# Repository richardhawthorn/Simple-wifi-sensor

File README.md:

### Description

Designed to collect and report various sensor readings over wifi.

### Sensors

- Temperature
- Humidity
- Light
- Vibration
- IR Receiver

### Other Features

- ESP8266
- 3.3V operation
- Mini USB power connector
- FTDI programming port
- IR Transmitter

### License

This work is licensed under a Creative Commons Attribution-ShareAlike 4.0 International License.

<br />
Designed by <a xmlns:cc="http://creativecommons.org/ns#" href="http://www.richardhawthorn.com" property="cc:attributionName" rel="cc:attributionURL" target="_blank">Richard Hawthorn</a><br />
<a rel="license" href="http://creativecommons.org/licenses/by-sa/4.0/" target="_blank">View License</a>

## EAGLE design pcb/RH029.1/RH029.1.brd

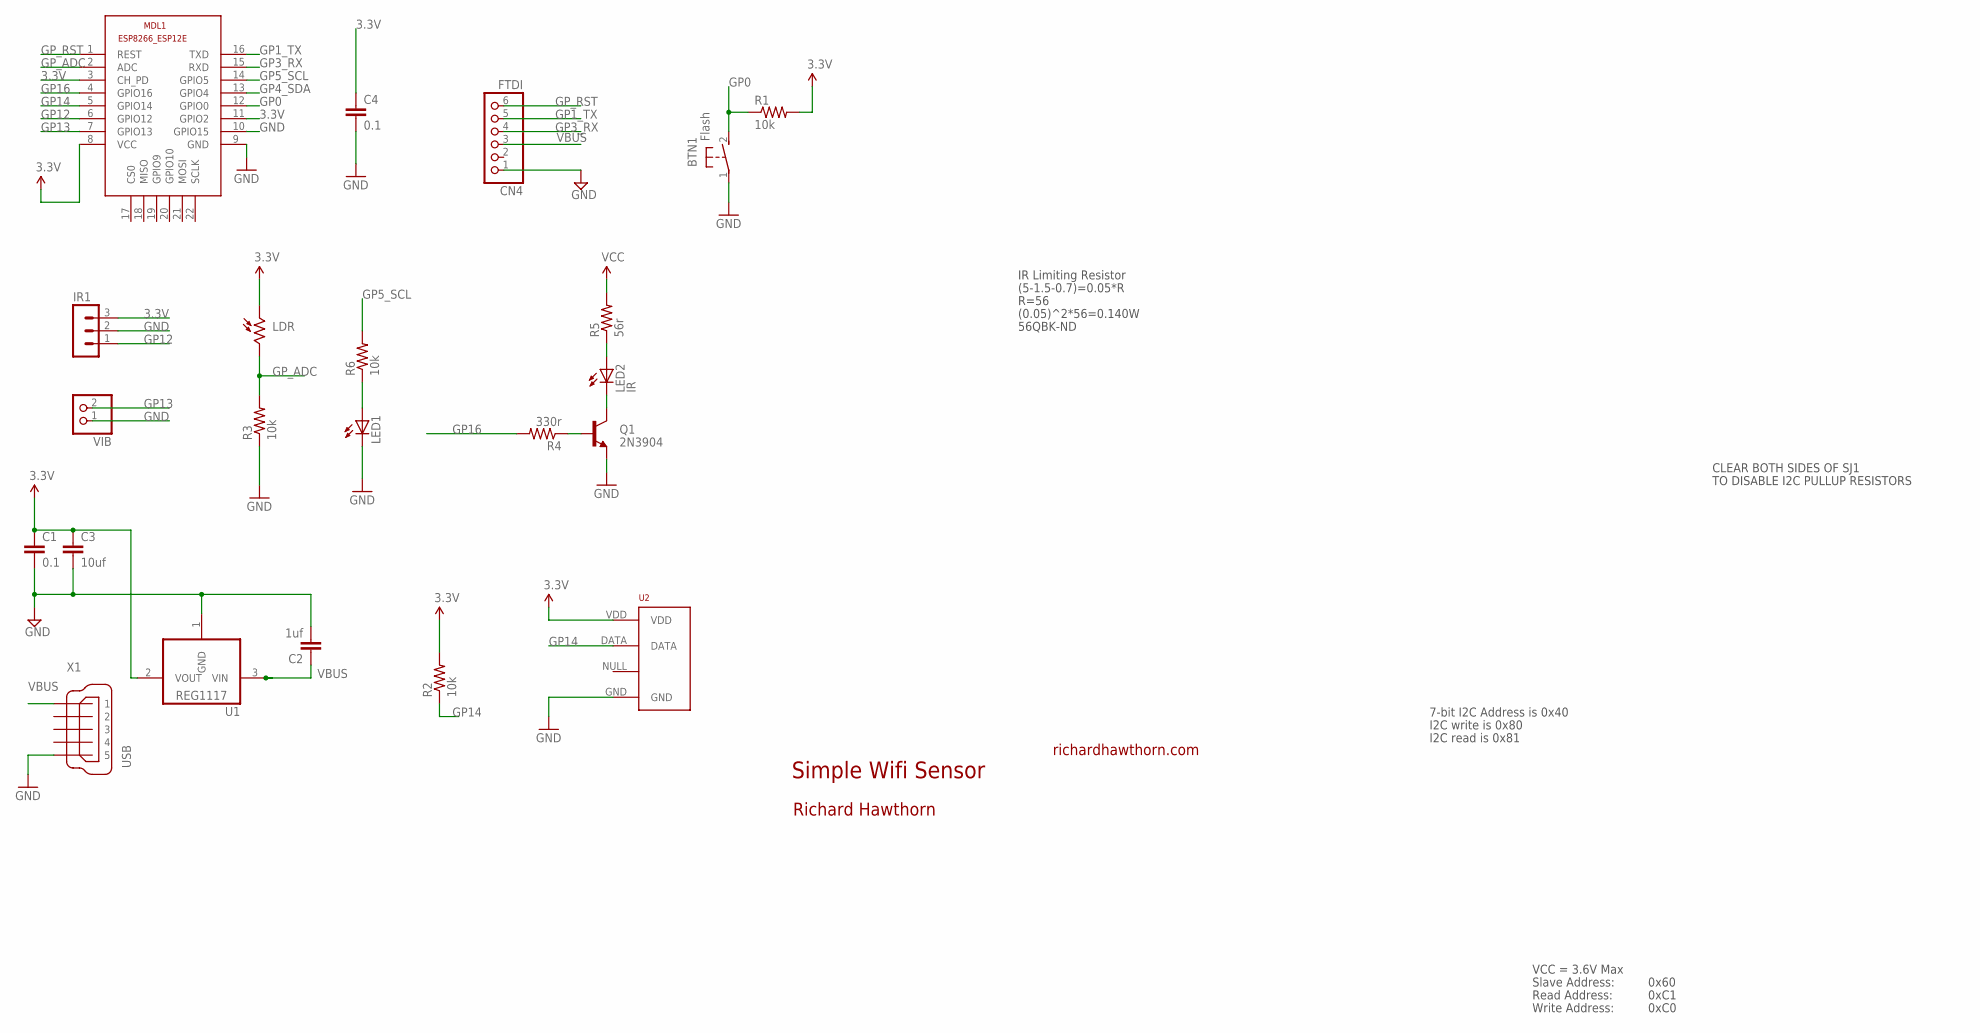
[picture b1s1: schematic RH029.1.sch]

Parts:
BTN1: Flash; DTS-3
C1, C4: 0.1; CAP-PTH-SMALL2
C2: 1uf; CAP-PTH-SMALL2
C3: 10uf; CAP-PTH-SMALL2
CN4: FTDI; 1X06
IR1: MA03-1
LDR: V1060_21; TO-5_V10
LED1: LED5MM
LED2: IR; LED5MM
MDL1: ESP8266-12EESP8266-ESP12E; ESP8266-ESP12E
Q1: 2N3904; TO-92
R1, R2, R3, R6: 10k; 0204/7
R4: 330r; 0204/7
R5: 56r; 0204/7
U1: REG1117; SOT223
U2: RHT03_DHT-22_AM2302RA; RHT03_DHT-22/RA
VIB: PINHD-1X2; 1X02
X1: USB; 32005-601

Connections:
3.3V: C1.1, C3.1, C4.1, IR1.3, LDR.1, MDL1.3 (CH_PD), MDL1.8 (VCC), MDL1.11 (GPIO2), R1.2, R2.2, R5.2, U1.2 (VOUT), U2.VDD
GND: BTN1.1, C1.2, C2.2, C3.2, C4.2, CN4.1, IR1.2, LED1.K (C), MDL1.9 (GND), MDL1.10 (GPIO15), Q1.1 (E), R3.1, U1.1 (GND), U2.GND, VIB.1, X1.5
GP0: BTN1.2, MDL1.12 (GPIO0), R1.1
GP1_TX: CN4.5, MDL1.16 (TXD)
GP3_RX: CN4.4, MDL1.15 (RXD)
GP4_SDA: MDL1.13 (GPIO4)
GP5_SCL: MDL1.14 (GPIO5), R6.2
GP12: IR1.1, MDL1.6 (GPIO12)
GP13: MDL1.7 (GPIO13), VIB.2
GP14: MDL1.5 (GPIO14), R2.1, U2.DATA
GP16: MDL1.4 (GPIO16), R4.2
GP_ADC: LDR.2, MDL1.2 (ADC), R3.2
GP_RST: CN4.6, MDL1.1 (REST)
unnamed: LED1.A, R6.1
unnamed: Q1.2 (B), R4.1
unnamed: LED2.K (C), Q1.3 (C)
unnamed: LED2.A, R5.1
VBUS: C2.1, CN4.3, U1.3 (VIN), X1.1

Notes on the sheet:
Simple Wifi Sensor
richardhawthorn.com
Richard Hawthorn
CLEAR BOTH SIDES OF SJ1
TO DISABLE I2C PULLUP RESISTORS
7-bit I2C Address is 0x40
I2C write is 0x80
I2C read is 0x81
VCC = 3.6V Max
Read Address:
Write Address:
Slave Address:
0x60
0xC1
0xC0
(5-1.5-0.7)=0.05*R
R=56
(0.05)^2*56=0.140W
IR Limiting Resistor
56QBK-ND

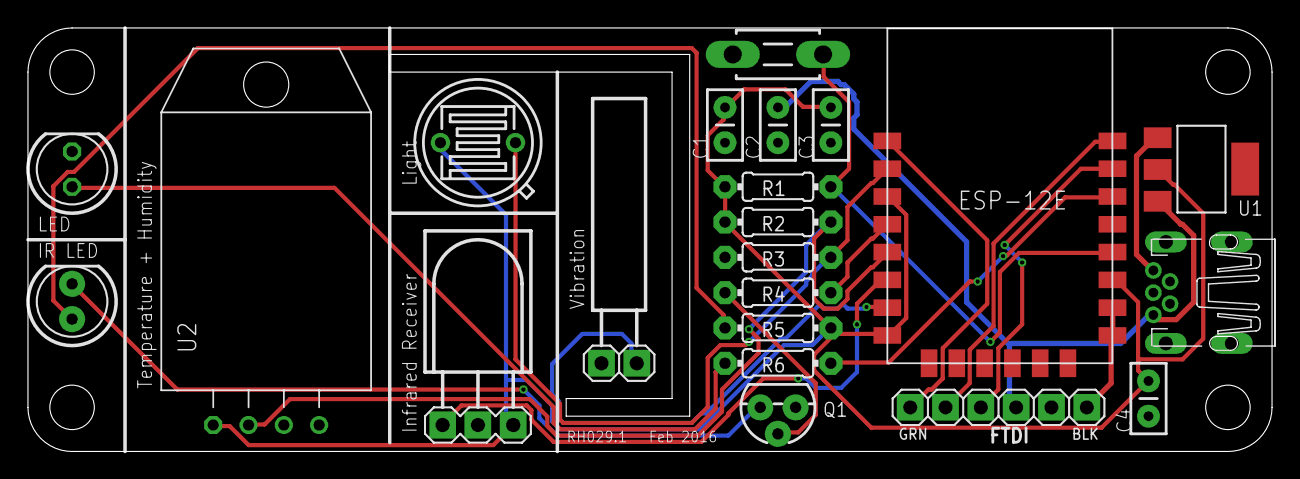
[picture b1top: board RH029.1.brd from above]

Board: 2 copper layers, 89.5 x 30.5 mm, 23 parts (1 on the bottom side), 17 nets.

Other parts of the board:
U$3: OSHW-LOGO-S

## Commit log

2016-11-10 add pcb files

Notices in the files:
parts and their libraries:
SparkFun-Aesthetics: Licensing: CC v3.0 Share-Alike You are welcome to use this library for commercial purposes.
